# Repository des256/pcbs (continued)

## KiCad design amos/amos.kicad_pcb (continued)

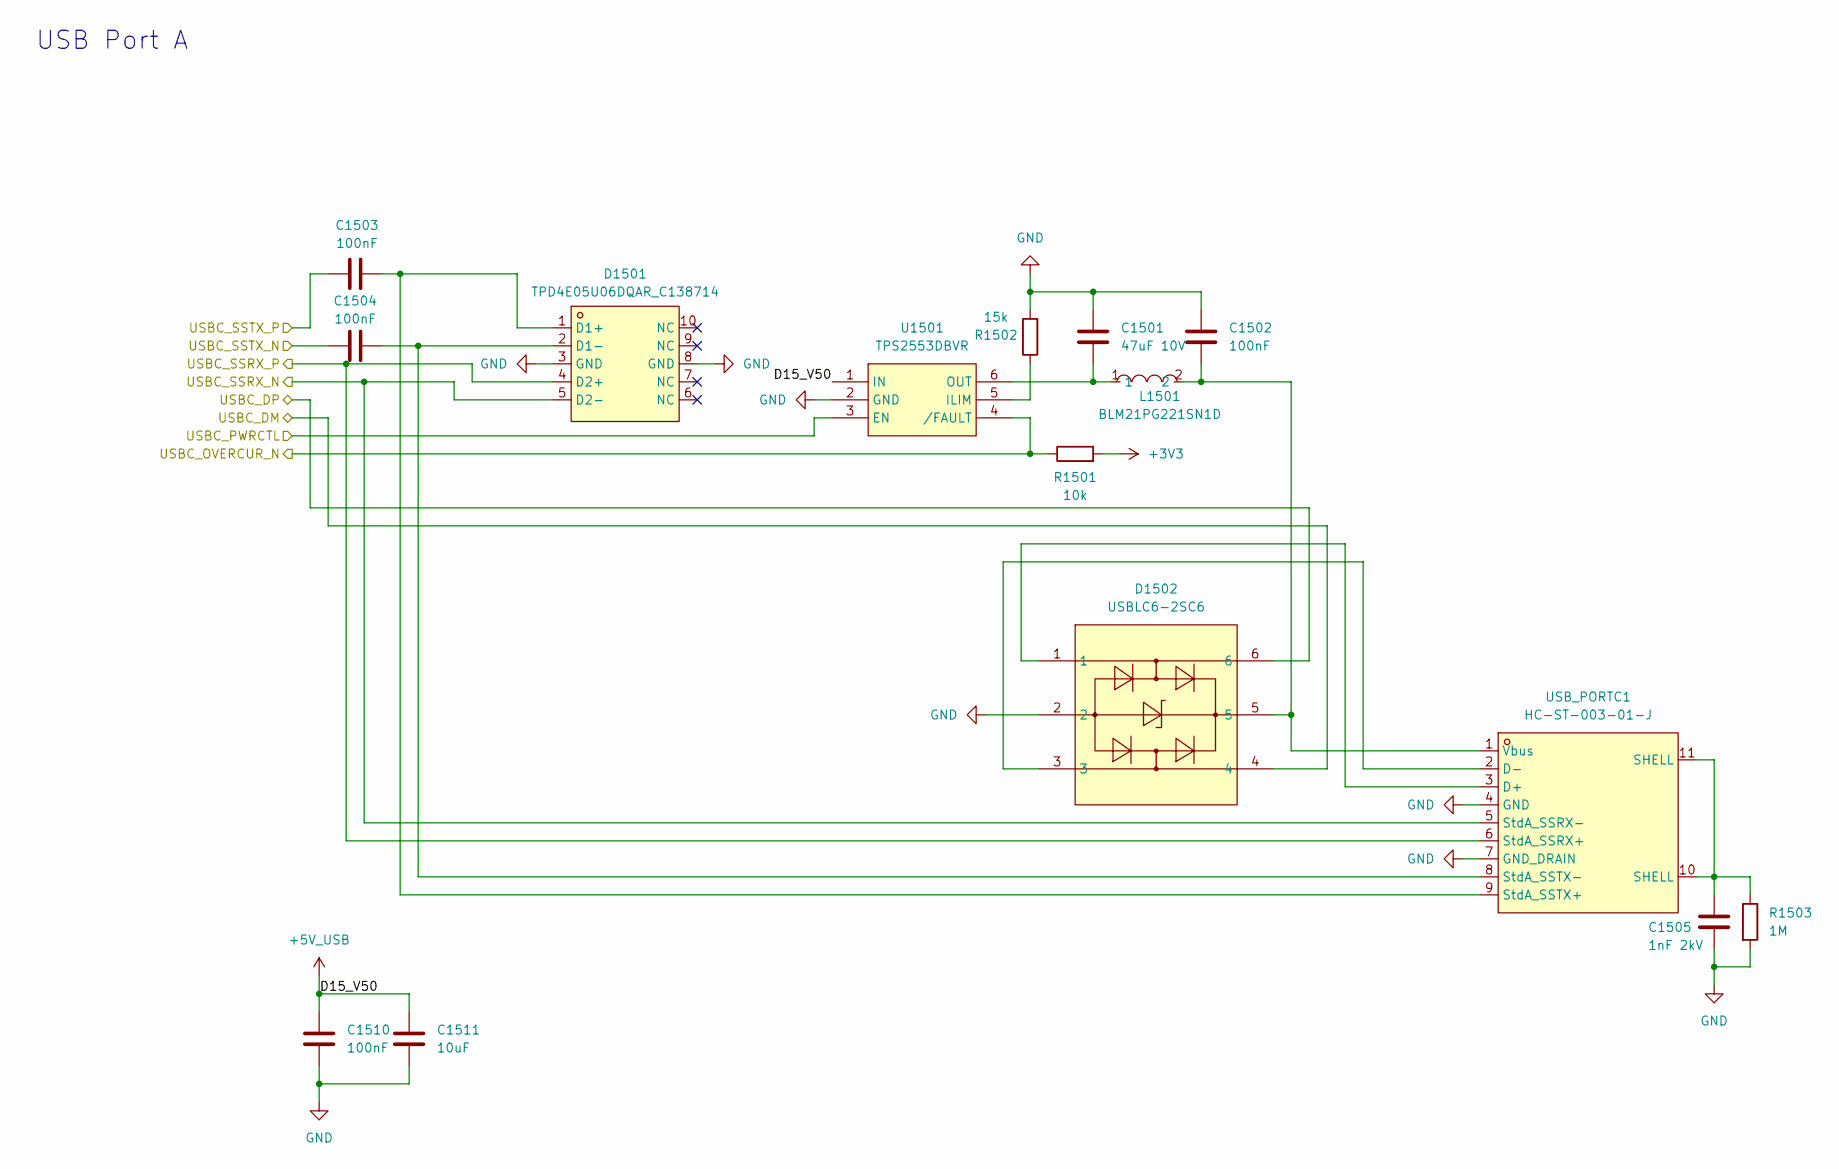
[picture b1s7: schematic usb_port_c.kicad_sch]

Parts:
C1501: 47uF 10V; C_1206_3216Metric; LCSC C96123
C1502, C1503, C1504: 100nF; C_0402_1005Metric; LCSC C307331
C1505: 1nF 2kV; C_1206_3216Metric; LCSC C9196
C1510: 100nF; C_0402_1005Metric; LCSC Part C14663
C1511: 10uF; C_0805_2012Metric; LCSC Part C15850
D1501: TPD4E05U06DQAR_C138714; USON-10_L2.5-W1.0-P0.50-BL; MPN TPD4E05U06DQAR; LCSC Part C138714
D1502: USBLC6-2SC6; SOT-23-6_L2.9-W1.6-P0.95-LS2.8-BL; MPN USBLC6-2SC6; LCSC Part C7519
L1501: BLM21PG221SN1D; L0805; MPN BLM21PG221SN1D; LCSC Part C85840
R1501: 10k; R_0402_1005Metric; LCSC C25744
R1502: 15k; R_0402_1005Metric; LCSC C25756
R1503: 1M; R_0402_1005Metric; LCSC C26083
U1501: TPS2553DBVR; SOT-23-6_L2.9-W1.6-P0.95-LS2.8-BR; MPN TPS2553DBVR; LCSC Part C55266
USB_PORTC1: HC-ST-003-01-J; USB-3.0-A-TH_HC-ST-003-01-Z; MPN HC-ST-003-01-J; LCSC Part C2845330

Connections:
+3V3: R1501.2; also elsewhere on the board
+5V_USB: C1510.1, C1511.1, U1501.1 (IN); also elsewhere on the board
/USBC_DM: D1502.4; also elsewhere on the board
/USBC_DP: D1502.6; also elsewhere on the board
/USBC_OVERCUR_N: R1501.1, U1501.4 (/FAULT); also elsewhere on the board
/USBC_PWRCTL: U1501.3 (EN); also elsewhere on the board
/USBC_SSRX_N: D1501.5 (D2-), USB_PORTC1.5 (StdA_SSRX-); also elsewhere on the board
/USBC_SSRX_P: D1501.4 (D2+), USB_PORTC1.6 (StdA_SSRX+); also elsewhere on the board
/USBC_SSTX_N: C1504.1; also elsewhere on the board
/USBC_SSTX_P: C1503.2; also elsewhere on the board
GND: C1501.1, C1502.1, C1505.2, C1510.2, C1511.2, D1501.3 (GND), D1501.8 (GND), D1502.2, R1502.2, R1503.2, U1501.2 (GND), USB_PORTC1.4 (GND), USB_PORTC1.7 (GND_DRAIN); also elsewhere on the board
unnamed: C1505.1, R1503.1, USB_PORTC1.10 (SHELL), USB_PORTC1.11 (SHELL)
unnamed: C1503.1, D1501.1 (D1+), USB_PORTC1.9 (StdA_SSTX+)
unnamed: C1504.2, D1501.2 (D1-), USB_PORTC1.8 (StdA_SSTX-)
unnamed: R1502.1, U1501.5 (ILIM)
unnamed: C1501.2, L1501.1, U1501.6 (OUT)
unnamed: D1502.1, USB_PORTC1.3 (D+)
unnamed: D1502.3, USB_PORTC1.2 (D-)
unnamed: C1502.2, D1502.5, L1501.2, USB_PORTC1.1 (Vbus)

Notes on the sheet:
USB Port A

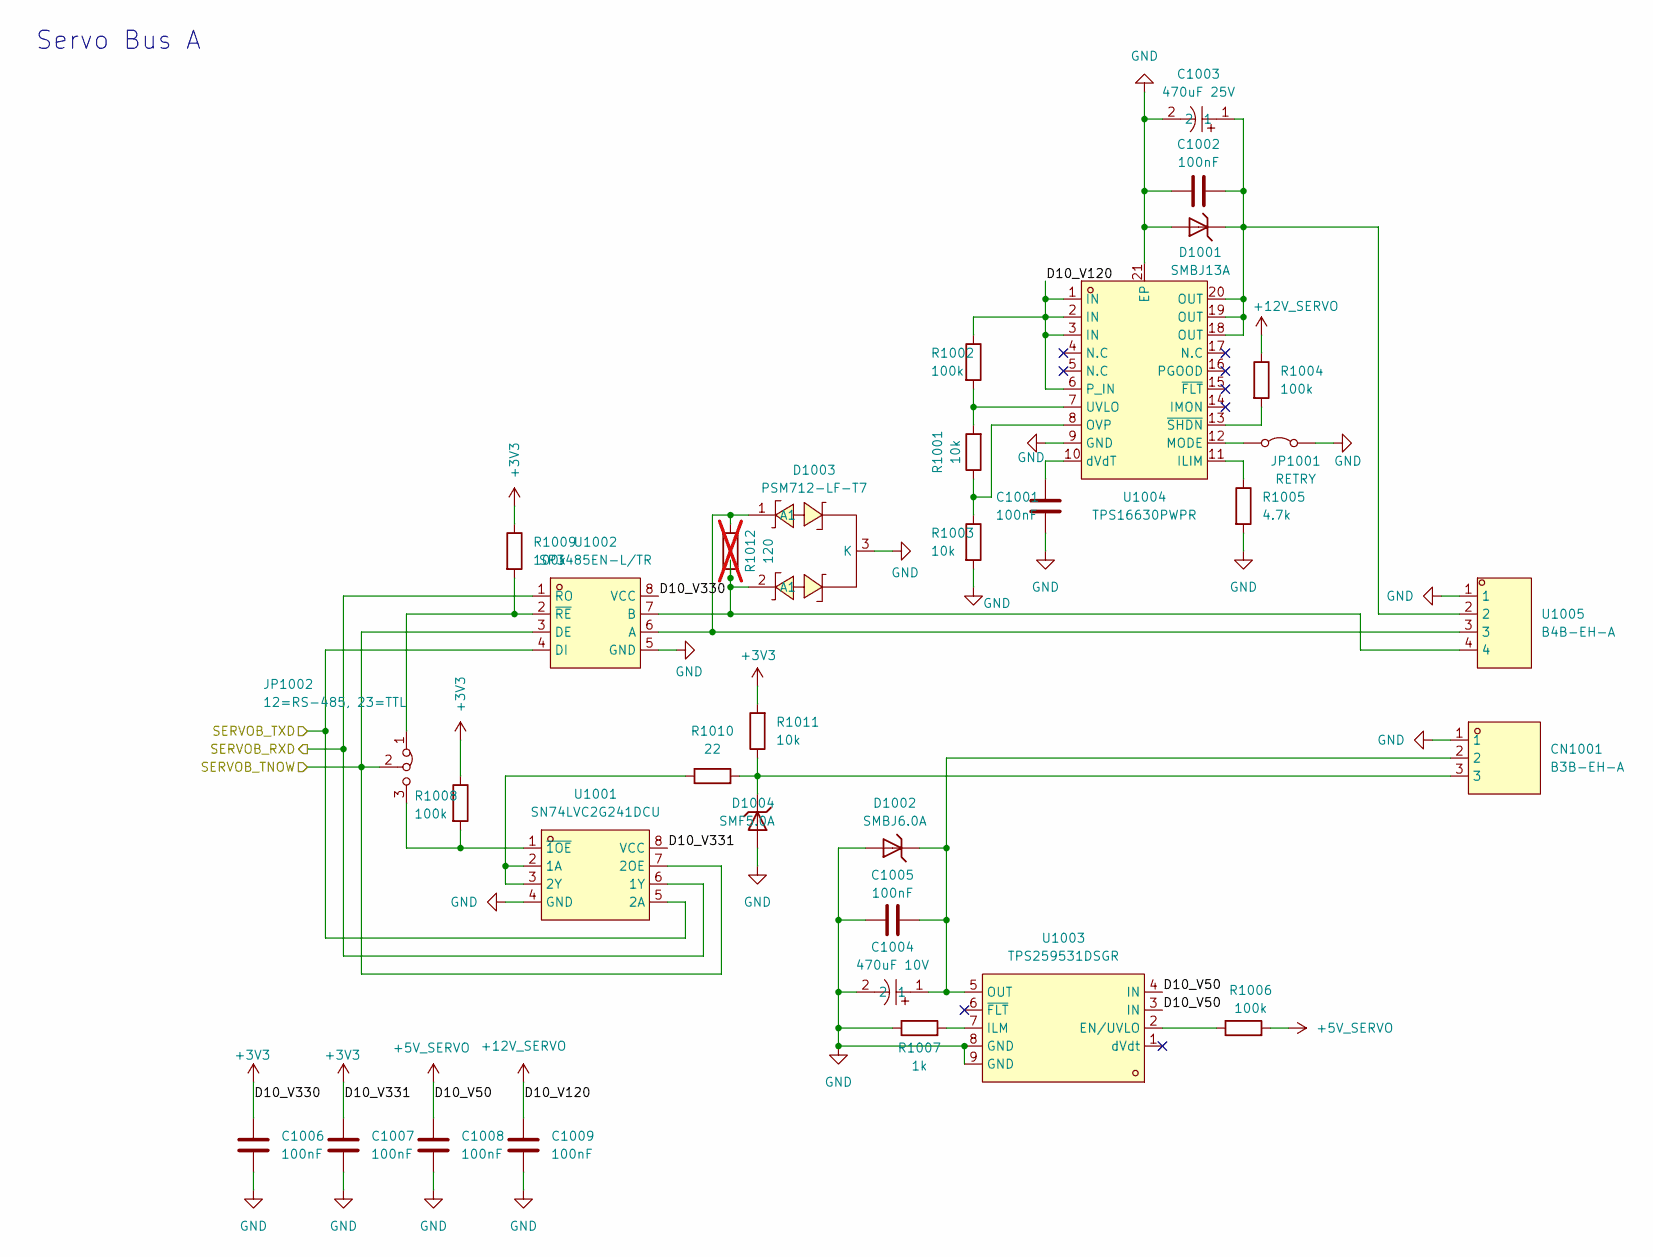
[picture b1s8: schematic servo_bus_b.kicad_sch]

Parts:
C1001, C1002, C1005: 100nF; C_0402_1005Metric; LCSC C307331
C1003: 470uF 25V; CP_Elec_8x10.5; LCSC C46550466
C1004: 470uF 10V; CP_Elec_6.3x7.7; LCSC C46550459
C1006, C1007, C1008, C1009: 100nF; C_0402_1005Metric; LCSC Part C14663
CN1001: B3B-EH-A; CONN-TH_B3B-EH-A-LF-SN; MPN B3B-EH-A(LF)(SN); LCSC Part C160259
D1001: SMBJ13A; SMB_L4.4-W3.6-LS5.3-RD; LCSC C19077567
D1002: SMBJ6.0A; SMB_L4.4-W3.6-LS5.3-RD; LCSC C19077560
D1003: PSM712-LF-T7; SOT-23-3_L3.0-W1.7-P0.95-LS2.9-BR; MPN PSM712-LF-T7; LCSC Part C32677
D1004: SMF5.0A; SOD-123FL_L2.8-W1.9-LS3.7-RD; LCSC C19077497
JP1001: RETRY; PinHeader_1x02_P2.54mm_Vertical; MPN PZ254V-11-02P; LCSC Part C492401
JP1002: 12=RS-485, 23=TTL; PinHeader_1x03_P2.54mm_Vertical; MPN PZ254V-11-03P; LCSC Part C2937625
R1001, R1003, R1011: 10k; R_0402_1005Metric; LCSC C25744
R1002, R1004, R1006, R1008, R1009: 100k; R_0402_1005Metric; LCSC C25741
R1005: 4.7k; R_0402_1005Metric; LCSC C25900
R1007: 1k; R_0402_1005Metric; LCSC C11702
R1010: 22; R_0402_1005Metric; LCSC C25092
R1012: 120; R_0603; LCSC C22787; not fitted
U1001: SN74LVC2G241DCU; VSSOP-8_L2.3-W2.0-P0.50-LS3.1-BR; MPN SN74LVC2G241DCUR; LCSC Part C10430
U1002: SP3485EN-L/TR; SOIC-8_L5.0-W4.0-P1.27-LS6.0-BL; MPN SP3485EN-L/TR; LCSC Part C8963
U1003: TPS259531DSGR; WSON-8_L2.0-W2.0-P0.50-TL-EP; MPN TPS259531DSGR; LCSC Part C2155674
U1004: TPS16630PWPR; HTSSOP-20_L6.5-W4.4-P0.65-LS6.4-TL-EP2.58; MPN TPS16630PWPR; LCSC Part C1849461
U1005: B4B-EH-A; CONN-TH_B4B-EH-A-LF-SN; MPN B4B-EH-A(LF)(SN); LCSC Part C160258

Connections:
+3V3: C1006.1, C1007.1, R1008.1, R1009.1, R1011.2, U1001.8 (VCC), U1002.8 (VCC); also elsewhere on the board
+5V_SERVO: C1008.1, R1006.2, U1003.3 (IN), U1003.4 (IN); also elsewhere on the board
+12V_SERVO: C1009.1, R1002.1, R1004.1, U1004.1 (IN), U1004.2 (IN), U1004.3 (IN), U1004.6 (P_IN); also elsewhere on the board
/SERVOB_RXD: U1001.6 (1Y), U1002.1 (RO); also elsewhere on the board
/SERVOB_TNOW: JP1002.2 (C), U1001.7 (2OE), U1002.3 (DE); also elsewhere on the board
/SERVOB_TXD: U1001.5 (2A), U1002.4 (DI); also elsewhere on the board
GND: C1001.2, C1002.1, C1003.2, C1004.2, C1005.1, C1006.2, C1007.2, C1008.2, C1009.2, CN1001.1, D1001.2, D1002.2, D1003.3 (K), D1004.2, JP1001.2 (B), R1003.2, R1005.2, R1007.1, U1001.4 (GND), U1002.5 (GND), U1003.8 (GND), U1003.9 (GND), U1004.9 (GND), U1004.21 (EP), U1005.1; also elsewhere on the board
unnamed: C1002.2, C1003.1, D1001.1, U1004.18 (OUT), U1004.19 (OUT), U1004.20 (OUT), U1005.2
unnamed: CN1001.3, D1004.1, R1010.2, R1011.1
unnamed: JP1001.1 (A), U1004.12 (MODE)
unnamed: JP1002.1 (A), R1009.2, U1002.2 (~RE)
unnamed: JP1002.3 (B), R1008.2, U1001.1 (~1OE)
unnamed: R1010.1, U1001.2 (1A), U1001.3 (2Y)
unnamed: D1003.1 (A1), R1012.1, U1002.6 (A), U1005.3
unnamed: D1003.2 (A1), R1012.2, U1002.7 (B), U1005.4
unnamed: R1006.1, U1003.2 (EN/UVLO)
unnamed: R1007.2, U1003.7 (ILM)
unnamed: C1004.1, C1005.2, CN1001.2, D1002.1, U1003.5 (OUT)
unnamed: R1005.1, U1004.11 (ILIM)
unnamed: R1001.1, R1003.1, U1004.8 (OVP)
unnamed: R1001.2, R1002.2, U1004.7 (UVLO)
unnamed: C1001.1, U1004.10 (dVdT)
unnamed: R1004.2, U1004.13 (~SHDN)

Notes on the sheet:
Servo Bus A

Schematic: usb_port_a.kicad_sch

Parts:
C1301: 47uF 10V; C_1206_3216Metric; LCSC C96123
C1302, C1303, C1304: 100nF; C_0402_1005Metric; LCSC C307331
C1305: 1nF 2kV; C_1206_3216Metric; LCSC C9196
C1306: 100nF; C_0402_1005Metric; LCSC Part C14663
C1307: 10uF; C_0805_2012Metric; LCSC Part C15850
D1301: TPD4E05U06DQAR_C138714; USON-10_L2.5-W1.0-P0.50-BL; MPN TPD4E05U06DQAR; LCSC Part C138714
D1302: USBLC6-2SC6; SOT-23-6_L2.9-W1.6-P0.95-LS2.8-BL; MPN USBLC6-2SC6; LCSC Part C7519
L1301: BLM21PG221SN1D; L0805; MPN BLM21PG221SN1D; LCSC Part C85840
R1301: 10k; R_0402_1005Metric; LCSC C25744
R1302: 15k; R_0402_1005Metric; LCSC C25756
R1303: 1M; R_0402_1005Metric; LCSC C26083
U1301: TPS2553DBVR; SOT-23-6_L2.9-W1.6-P0.95-LS2.8-BR; MPN TPS2553DBVR; LCSC Part C55266
USB_PORTA1: HC-ST-003-01-J; USB-3.0-A-TH_HC-ST-003-01-Z; MPN HC-ST-003-01-J; LCSC Part C2845330

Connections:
+3V3: R1301.2; also elsewhere on the board
+5V_USB: C1306.1, C1307.1, U1301.1 (IN); also elsewhere on the board
/USBA_DM: D1302.4; also elsewhere on the board
/USBA_DP: D1302.6; also elsewhere on the board
/USBA_OVERCUR_N: R1301.1, U1301.4 (/FAULT); also elsewhere on the board
/USBA_PWRCTL: U1301.3 (EN); also elsewhere on the board
/USBA_SSRX_N: D1301.5 (D2-), USB_PORTA1.5 (StdA_SSRX-); also elsewhere on the board
/USBA_SSRX_P: D1301.4 (D2+), USB_PORTA1.6 (StdA_SSRX+); also elsewhere on the board
/USBA_SSTX_N: C1304.1; also elsewhere on the board
/USBA_SSTX_P: C1303.2; also elsewhere on the board
GND: C1301.1, C1302.1, C1305.2, C1306.2, C1307.2, D1301.3 (GND), D1301.8 (GND), D1302.2, R1302.2, R1303.2, U1301.2 (GND), USB_PORTA1.4 (GND), USB_PORTA1.7 (GND_DRAIN); also elsewhere on the board
unnamed: C1305.1, R1303.1, USB_PORTA1.10 (SHELL), USB_PORTA1.11 (SHELL)
unnamed: C1303.1, D1301.1 (D1+), USB_PORTA1.9 (StdA_SSTX+)
unnamed: C1304.2, D1301.2 (D1-), USB_PORTA1.8 (StdA_SSTX-)
unnamed: R1302.1, U1301.5 (ILIM)
unnamed: C1301.2, L1301.1, U1301.6 (OUT)
unnamed: D1302.1, USB_PORTA1.3 (D+)
unnamed: D1302.3, USB_PORTA1.2 (D-)
unnamed: C1302.2, D1302.5, L1301.2, USB_PORTA1.1 (Vbus)

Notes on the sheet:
USB Port A

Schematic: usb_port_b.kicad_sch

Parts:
C1401: 47uF 10V; C_1206_3216Metric; LCSC C96123
C1402, C1403, C1404: 100nF; C_0402_1005Metric; LCSC C307331
C1405: 1nF 2kV; C_1206_3216Metric; LCSC C9196
C1408: 100nF; C_0402_1005Metric; LCSC Part C14663
C1409: 10uF; C_0805_2012Metric; LCSC Part C15850
D1401: TPD4E05U06DQAR_C138714; USON-10_L2.5-W1.0-P0.50-BL; MPN TPD4E05U06DQAR; LCSC Part C138714
D1402: USBLC6-2SC6; SOT-23-6_L2.9-W1.6-P0.95-LS2.8-BL; MPN USBLC6-2SC6; LCSC Part C7519
L1401: BLM21PG221SN1D; L0805; MPN BLM21PG221SN1D; LCSC Part C85840
R1401: 10k; R_0402_1005Metric; LCSC C25744
R1402: 15k; R_0402_1005Metric; LCSC C25756
R1403: 1M; R_0402_1005Metric; LCSC C26083
U1401: TPS2553DBVR; SOT-23-6_L2.9-W1.6-P0.95-LS2.8-BR; MPN TPS2553DBVR; LCSC Part C55266
USB_PORTB1: HC-ST-003-01-J; USB-3.0-A-TH_HC-ST-003-01-Z; MPN HC-ST-003-01-J; LCSC Part C2845330

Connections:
+3V3: R1401.2; also elsewhere on the board
+5V_USB: C1408.1, C1409.1, U1401.1 (IN); also elsewhere on the board
/USBB_DM: D1402.4; also elsewhere on the board
/USBB_DP: D1402.6; also elsewhere on the board
/USBB_OVERCUR_N: R1401.1, U1401.4 (/FAULT); also elsewhere on the board
/USBB_PWRCTL: U1401.3 (EN); also elsewhere on the board
/USBB_SSRX_N: D1401.5 (D2-), USB_PORTB1.5 (StdA_SSRX-); also elsewhere on the board
/USBB_SSRX_P: D1401.4 (D2+), USB_PORTB1.6 (StdA_SSRX+); also elsewhere on the board
/USBB_SSTX_N: C1404.1; also elsewhere on the board
/USBB_SSTX_P: C1403.2; also elsewhere on the board
GND: C1401.1, C1402.1, C1405.2, C1408.2, C1409.2, D1401.3 (GND), D1401.8 (GND), D1402.2, R1402.2, R1403.2, U1401.2 (GND), USB_PORTB1.4 (GND), USB_PORTB1.7 (GND_DRAIN); also elsewhere on the board
unnamed: C1405.1, R1403.1, USB_PORTB1.10 (SHELL), USB_PORTB1.11 (SHELL)
unnamed: C1403.1, D1401.1 (D1+), USB_PORTB1.9 (StdA_SSTX+)
unnamed: C1404.2, D1401.2 (D1-), USB_PORTB1.8 (StdA_SSTX-)
unnamed: R1402.1, U1401.5 (ILIM)
unnamed: C1401.2, L1401.1, U1401.6 (OUT)
unnamed: D1402.1, USB_PORTB1.3 (D+)
unnamed: D1402.3, USB_PORTB1.2 (D-)
unnamed: C1402.2, D1402.5, L1401.2, USB_PORTB1.1 (Vbus)

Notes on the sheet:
USB Port A

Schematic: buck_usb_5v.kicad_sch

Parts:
C501: 4.7nF; C_0402_1005Metric; LCSC C1538
C502: 47pF; C_0402_1005Metric; LCSC C1567
C503: 100nF; C_0402_1005Metric; LCSC C307331
C504, C505, C506, C507: 2.2uF 50V; C_1206_3216Metric; LCSC Part C50254
C508, C509, C510, C511, C512, C513: 47uF 10V; C_1206_3216Metric; LCSC Part C96123
D501: B560C; SMC_L7.1-W6.2-LS8.1-RD; MPN B560C-13-F; LCSC Part C85100
D502: LED Green; LED_0805_2012Metric; LCSC C2297
L501: 7.2uH 6A; IND-SMD_L10.2-W10.2_7447798720; MPN 7447798720; LCSC Part C105681
R501: 442k; R_0402_1005Metric; LCSC C5101; not fitted
R502: 90.9k; R_0402_1005Metric; LCSC C26989; not fitted
R503: 200k; R_0402_1005Metric; LCSC C25764
R504: 15k; R_0402_1005Metric; LCSC C25756
R505: 53.6k; R_0402_1005Metric; LCSC C453713
R506: 10k; R_0402_1005Metric; LCSC C25744
R507: 1k; R_0402_1005Metric; LCSC C11702
TP501: +5V_USB; TestPoint_Pad_1.0x1.0mm
U501: TPS54560DDAR; SOIC-8_L5.0-W4.0-P1.27-LS6.0-BL-EP2.0; MPN TPS54560DDAR; LCSC Part C31966

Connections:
+5V_USB: C508.1, C509.1, C510.1, C511.1, C512.1, C513.1, L501.2, R505.2, R507.2, TP501.1 (1_1); also elsewhere on the board
+19V: C504.1, C505.1, C506.1, C507.1, R501.1, U501.2 (VIN); also elsewhere on the board
GND: C501.1, C502.2, C504.2, C505.2, C506.2, C507.2, C508.2, C509.2, C510.2, C511.2, C512.2, C513.2, D501.2 (A), D502.1 (K), R502.2, R503.2, R506.2, U501.7 (GND), U501.9 (EP); also elsewhere on the board
unnamed: C501.2, R504.2
unnamed: C503.2, D501.1 (K), L501.1, U501.8 (SW)
unnamed: D502.2 (A), R507.1
unnamed: C503.1, U501.1 (BOOT)
unnamed: C502.1, R504.1, U501.6 (COMP)
unnamed: R501.2, R502.1, U501.3 (EN)
unnamed: R505.1, R506.1, U501.5 (FB)
unnamed: R503.1, U501.4 (RT/CLK)

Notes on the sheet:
5V Buck Converter for USB Devices

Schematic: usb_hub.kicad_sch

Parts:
C701, C702: 30pF; C_0402_1005Metric; LCSC Part C1658
C703, C708, C718: 10uF; C_0805_2012Metric; LCSC Part C15850
C704, C706, C707, C709, C710, C711, C712, C713, C714, C715, C716: 100nF; C_0402_1005Metric; LCSC Part C14663
C705: 4.7uF; C_0805_2012Metric; LCSC Part C1779
C717: 22uF; C_0805_2012Metric; LCSC Part C45783
FB701: BLM18PG121SN1D; L0603; LCSC C14709
R701: 9.53k; R_0402_1005Metric; LCSC C96273
R702: 1M; R_0402_1005Metric; LCSC C26083
R703, R705, R706, R707, R708: 10k; R_0402_1005Metric; LCSC C25744
R704: 90.9k; R_0402_1005Metric; LCSC C26989
TP701: GRSTz; TestPoint_Pad_1.0x1.0mm
U701: TUSB8041IRGCR; QFN-64_L9.0-W9.0-P0.50-BL-EP7.2; MPN TUSB8041IRGCR; LCSC Part C544686
Y701: 24MHz 18pF; OSC-SMD_4P-L3.2-W2.5-BL; LCSC C70571

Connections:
+1V1: C717.1, FB701.2; also elsewhere on the board
+3V3: C704.1, C705.1, C706.1, C707.1, C708.1, R703.2, R706.1, R707.2, R708.2, U701.16 (VDD33), U701.34 (VDD33), U701.52 (VDD33), U701.63 (VDD33); also elsewhere on the board
/SERVO_DM: U701.25 (USB_DM_DN4); also elsewhere on the board
/SERVO_DP: U701.24 (USB_DP_DN4); also elsewhere on the board
/USB Hub/D7_V110: C709.1, C710.1, C711.1, C712.1, C713.1, C714.1, C715.1, C716.1, C718.1, FB701.1, U701.5 (VDD), U701.8 (VDD), U701.13 (VDD), U701.21 (VDD), U701.28 (VDD), U701.31 (VDD), U701.51 (VDD), U701.57 (VDD)
/USBA_DM: U701.2 (USB_DM_DN1); also elsewhere on the board
/USBA_DP: U701.1 (USB_DP_DN1); also elsewhere on the board
/USBA_OVERCUR_N: R708.1, U701.46 (OVERCUR1z); also elsewhere on the board
/USBA_PWRCTL: U701.36 (PWRCTL1/BATEN1); also elsewhere on the board
/USBA_SSRX_N: U701.7 (USB_SSRXM_DN1); also elsewhere on the board
/USBA_SSRX_P: U701.6 (USB_SSRXP_DN1); also elsewhere on the board
/USBA_SSTX_N: U701.4 (USB_SSTXM_DN1); also elsewhere on the board
/USBA_SSTX_P: U701.3 (USB_SSTXP_DN1); also elsewhere on the board
/USBB_DM: U701.10 (USB_DM_DN2); also elsewhere on the board
/USBB_DP: U701.9 (USB_DP_DN2); also elsewhere on the board
/USBB_OVERCUR_N: R707.1, U701.47 (OVERCUR2z); also elsewhere on the board
/USBB_PWRCTL: U701.35 (PWRCTL2/BATEN2); also elsewhere on the board
/USBB_SSRX_N: U701.15 (USB_SSRXM_DN2); also elsewhere on the board
/USBB_SSRX_P: U701.14 (USB_SSRXP_DN2); also elsewhere on the board
/USBB_SSTX_N: U701.12 (USB_SSTXM_DN2); also elsewhere on the board
/USBB_SSTX_P: U701.11 (USB_SSTXP_DN2); also elsewhere on the board
/USBC_DM: U701.18 (USB_DM_DN3); also elsewhere on the board
/USBC_DP: U701.17 (USB_DP_DN3); also elsewhere on the board
/USBC_OVERCUR_N: R706.2, U701.44 (OVERCUR3z); also elsewhere on the board
/USBC_PWRCTL: U701.33 (PWRCTL3/BATEN3); also elsewhere on the board
/USBC_SSRX_N: U701.23 (USB_SSRXM_DN3); also elsewhere on the board
/USBC_SSRX_P: U701.22 (USB_SSRXP_DN3); also elsewhere on the board
/USBC_SSTX_N: U701.20 (USB_SSTXM_DN3); also elsewhere on the board
/USBC_SSTX_P: U701.19 (USB_SSTXP_DN3); also elsewhere on the board
/USBU_DM: U701.54 (USB_DM_UP); also elsewhere on the board
/USBU_DP: U701.53 (USB_DP_UP); also elsewhere on the board
/USBU_SSRX_M: U701.59 (USB_SSRXM_UP); also elsewhere on the board
/USBU_SSRX_P: U701.58 (USB_SSRXP_UP); also elsewhere on the board
/USBU_SSTX_M: U701.56 (USB_SSTXM_UP); also elsewhere on the board
/USBU_SSTX_P: U701.55 (USB_SSTXP_UP); also elsewhere on the board
/USB_VBUS: R704.2; also elsewhere on the board
GND: C701.1, C702.1, C703.2, C704.2, C705.2, C706.2, C707.2, C708.2, C709.2, C710.2, C711.2, C712.2, C713.2, C714.2, C715.2, C716.2, C717.2, C718.2, R701.2, R705.2, U701.49 (TEST), U701.65 (VSS), Y701.2 (GND), Y701.4 (GND); also elsewhere on the board
unnamed: C703.1, R703.1, TP701.1 (1_1), U701.50 (GRSTz)
unnamed: R701.1, U701.64 (USB_R1)
unnamed: R704.1, R705.1, U701.48 (USB_VBUS)
unnamed: C701.2, R702.1, U701.62 (XI), Y701.1 (OSC)
unnamed: C702.2, R702.2, U701.61 (XO), Y701.3 (OSC)

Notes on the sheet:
USB Hub

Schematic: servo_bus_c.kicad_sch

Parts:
C1101, C1102, C1105: 100nF; C_0402_1005Metric; LCSC C307331
C1103: 470uF 25V; CP_Elec_8x10.5; LCSC C46550466
C1104: 470uF 10V; CP_Elec_6.3x7.7; LCSC C46550459
C1106, C1107, C1108, C1109: 100nF; C_0402_1005Metric; LCSC Part C14663
CN1101: B3B-EH-A; CONN-TH_B3B-EH-A-LF-SN; MPN B3B-EH-A(LF)(SN); LCSC Part C160259
D1101: SMBJ13A; SMB_L4.4-W3.6-LS5.3-RD; LCSC C19077567
D1102: SMBJ6.0A; SMB_L4.4-W3.6-LS5.3-RD; LCSC C19077560
D1103: PSM712-LF-T7; SOT-23-3_L3.0-W1.7-P0.95-LS2.9-BR; MPN PSM712-LF-T7; LCSC Part C32677
D1104: SMF5.0A; SOD-123FL_L2.8-W1.9-LS3.7-RD; LCSC C19077497
JP1101: RETRY; PinHeader_1x02_P2.54mm_Vertical; MPN PZ254V-11-02P; LCSC Part C492401
JP1102: 12=RS-485, 23=TTL; PinHeader_1x03_P2.54mm_Vertical; MPN PZ254V-11-03P; LCSC Part C2937625
R1101, R1103, R1111: 10k; R_0402_1005Metric; LCSC C25744
R1102, R1104, R1106, R1108, R1109: 100k; R_0402_1005Metric; LCSC C25741
R1105: 4.7k; R_0402_1005Metric; LCSC C25900
R1107: 1k; R_0402_1005Metric; LCSC C11702
R1110: 22; R_0402_1005Metric; LCSC C25092
R1112: 120; R_0603; LCSC C22787; not fitted
U1101: SN74LVC2G241DCU; VSSOP-8_L2.3-W2.0-P0.50-LS3.1-BR; MPN SN74LVC2G241DCUR; LCSC Part C10430
U1102: SP3485EN-L/TR; SOIC-8_L5.0-W4.0-P1.27-LS6.0-BL; MPN SP3485EN-L/TR; LCSC Part C8963
U1103: TPS259531DSGR; WSON-8_L2.0-W2.0-P0.50-TL-EP; MPN TPS259531DSGR; LCSC Part C2155674
U1104: TPS16630PWPR; HTSSOP-20_L6.5-W4.4-P0.65-LS6.4-TL-EP2.58; MPN TPS16630PWPR; LCSC Part C1849461
U1105: B4B-EH-A; CONN-TH_B4B-EH-A-LF-SN; MPN B4B-EH-A(LF)(SN); LCSC Part C160258

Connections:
+3V3: C1106.1, C1107.1, R1108.1, R1109.1, R1111.2, U1101.8 (VCC), U1102.8 (VCC); also elsewhere on the board
+5V_SERVO: C1108.1, R1106.2, U1103.3 (IN), U1103.4 (IN); also elsewhere on the board
+12V_SERVO: C1109.1, R1102.1, R1104.1, U1104.1 (IN), U1104.2 (IN), U1104.3 (IN), U1104.6 (P_IN); also elsewhere on the board
/SERVOC_RXD: U1101.6 (1Y), U1102.1 (RO); also elsewhere on the board
/SERVOC_TNOW: JP1102.2 (C), U1101.7 (2OE), U1102.3 (DE); also elsewhere on the board
/SERVOC_TXD: U1101.5 (2A), U1102.4 (DI); also elsewhere on the board
GND: C1101.2, C1102.1, C1103.2, C1104.2, C1105.1, C1106.2, C1107.2, C1108.2, C1109.2, CN1101.1, D1101.2, D1102.2, D1103.3 (K), D1104.2, JP1101.2 (B), R1103.2, R1105.2, R1107.1, U1101.4 (GND), U1102.5 (GND), U1103.8 (GND), U1103.9 (GND), U1104.9 (GND), U1104.21 (EP), U1105.1; also elsewhere on the board
unnamed: C1102.2, C1103.1, D1101.1, U1104.18 (OUT), U1104.19 (OUT), U1104.20 (OUT), U1105.2
unnamed: CN1101.3, D1104.1, R1110.2, R1111.1
unnamed: JP1101.1 (A), U1104.12 (MODE)
unnamed: JP1102.1 (A), R1109.2, U1102.2 (~RE)
unnamed: JP1102.3 (B), R1108.2, U1101.1 (~1OE)
unnamed: R1110.1, U1101.2 (1A), U1101.3 (2Y)
unnamed: D1103.1 (A1), R1112.1, U1102.6 (A), U1105.3
unnamed: D1103.2 (A1), R1112.2, U1102.7 (B), U1105.4
unnamed: R1106.1, U1103.2 (EN/UVLO)
unnamed: R1107.2, U1103.7 (ILM)
unnamed: C1104.1, C1105.2, CN1101.2, D1102.1, U1103.5 (OUT)
unnamed: R1105.1, U1104.11 (ILIM)
unnamed: R1101.1, R1103.1, U1104.8 (OVP)
unnamed: R1101.2, R1102.2, U1104.7 (UVLO)
unnamed: C1101.1, U1104.10 (dVdT)
unnamed: R1104.2, U1104.13 (~SHDN)

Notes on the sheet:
Servo Bus A

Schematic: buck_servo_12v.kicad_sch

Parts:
C301, C307: 100nF; C_0402_1005Metric; LCSC C307331
C302: 47pF; C_0402_1005Metric; LCSC C1567
C303: 3.3nF; C_0402_1005Metric; LCSC C26404
C304: 680pF; C_0402_1005Metric; LCSC C1541
C305: 4.7uF 16V; C_0603_1608Metric; LCSC C19666
C306: 10pF; C_0402_1005Metric; LCSC C32949
C308: 100pF; C_0603_1608Metric; LCSC C14858; not fitted
C309: 100nF 100V; C_0805_2012Metric; LCSC Part C28233
C310, C311, C312, C313, C314: 4.7uF 50V; C_1206_3216Metric; LCSC Part C29823
C315, C316, C317, C318, C319, C320: 22uF 25V; C_1206_3216Metric; LCSC Part C12891
C321, C322: 470uF 25V; CAP-SMD_BD8.0-L8.3-W8.3-LS9.0-FD_H10.5; LCSC Part C46550466
D301: SS14; D_SMA; LCSC C2480
D302: LED Green; LED_0805_2012Metric; LCSC C2297
JP301: SYNCIN GND OR PGOOD; SolderJumper-3_P1.3mm_Bridged12_Pad1.0x1.5mm
L301: 4.7uH 20A; IND-SMD_L13.5-W12.6; MPN TMPA1265SP-4R7MN-D; LCSC Part C2880057
Q301, Q302: CSD18532Q5B; SON-8_L5.0-W6.0-P1.27-BL-1; MPN CSD18532Q5B; LCSC Part C882766
R301: 100k; R_0402_1005Metric; LCSC C25741
R302: 10k; R_0402_1005Metric; LCSC C25744
R303: 22k; R_0402_1005Metric; LCSC C25768
R304: 15k; R_0402_1005Metric; LCSC C25756
R305: 3.3k; R_0402_1005Metric; LCSC C25890
R306: 200; R_0402_1005Metric; LCSC C25087
R307: 47k; R_0402_1005Metric; LCSC C25792
R308: 20k; R_0402_1005Metric; LCSC C25765
R309: 2.2; R_0402_1005Metric; LCSC C25101
R310: 220; R_0402_1005Metric; LCSC C25091
R311: 4.7k; R_0402_1005Metric; LCSC C25900
R312: 2.2; R_0603; LCSC C22939; not fitted
TP301: +12V_SERVO; TestPoint_Pad_1.0x1.0mm
U301: LM5145RGYR; VQFN-20_L4.5-W3.5-P0.50-BL-EP; MPN LM5145RGYR; LCSC Part C485912

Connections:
+12V_SERVO: C315.1, C316.1, C317.1, C318.1, C319.1, C320.1, C321.1, C322.1, D301.2 (A), L301.2, R306.1, R307.1, R311.1, TP301.1 (1_1); also elsewhere on the board
+19V: C309.1, C310.1, C311.1, C312.1, C313.1, C314.1, Q301.5 (D), Q301.6 (D), Q301.7 (D), Q301.8 (D), Q301.9 (EP), R301.1, U301.20 (VIN); also elsewhere on the board
GND: C301.2, C305.2, C306.2, C308.2, C309.2, C310.2, C311.2, C312.2, C313.2, C314.2, C315.2, C316.2, C317.2, C318.2, C319.2, C320.2, C321.2, C322.2, D302.1 (K), JP301.1 (A), Q302.1 (S), Q302.2 (S), Q302.3 (S), R302.2, R303.1, R305.2, U301.6 (AGND), U301.12 (PGND), U301.15 (EP), U301.21 (EP); also elsewhere on the board
unnamed: C303.2, R304.1
unnamed: C304.1, R306.2
unnamed: C307.1, R309.2
unnamed: C308.1, R312.2
unnamed: C305.1, D301.1 (K), JP301.3 (B), R308.1, U301.14 (VCC)
unnamed: D302.2 (A), R311.2
unnamed: JP301.2 (C), U301.8 (SYNCIN)
unnamed: Q301.4 (G), U301.18 (HO)
unnamed: C307.2, L301.1, Q301.1 (S), Q301.2 (S), Q301.3 (S), Q302.5 (D), Q302.6 (D), Q302.7 (D), Q302.8 (D), Q302.9 (EP), R310.2, R312.1, U301.19 (SW)
unnamed: Q302.4 (G), U301.13 (LO)
unnamed: R309.1, U301.17 (BST)
unnamed: C302.1, R304.2, U301.4 (COMP)
unnamed: R301.2, R302.1, U301.1 (EN/UVLO)
unnamed: C302.2, C303.1, C304.2, R305.1, R307.2, U301.5 (FB)
unnamed: C306.1, R310.1, U301.11 (ILIM)
unnamed: R308.2, U301.10 (PGOOD)
unnamed: R303.2, U301.2 (RT)
unnamed: C301.1, U301.3 (SS/TRK)

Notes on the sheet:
12V Buck Converter for Large Servo

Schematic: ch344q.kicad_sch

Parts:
C801, C802: 33pF; C_0402_1005Metric; LCSC C1562
C803: 100nF; C_0402_1005Metric; LCSC C307331
C804, C805, C806, C807: 100nF; C_0402_1005Metric; LCSC Part C14663
C808: 10uF; C_0805_2012Metric; LCSC Part C15850
D801: USBLC6-2SC6; SOT-23-6_L2.9-W1.6-P0.95-LS2.8-BL; MPN USBLC6-2SC6; LCSC Part C7519
D802: LED Yellow; LED_0805_2012Metric; LCSC C2296
R801: 10k; R_0402_1005Metric; LCSC C25744
R802: 1k; R_0402_1005Metric; LCSC C11702
R803, R804, R805, R806: 4.7k; R_0402_1005Metric; LCSC C25900
TP801: RESET; TestPoint_Pad_1.0x1.0mm
U801: CH344Q_C2988084; LQFP-48_L7.0-W7.0-P0.50-LS9.0-BL; MPN CH344Q; LCSC Part C2988084
Y801: 8MHz 20pF; Crystal_SMD_5032-2Pin_5.0x3.2mm; LCSC C115962

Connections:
+3V3: C804.1, C805.1, C806.1, C807.1, C808.1, D801.5, R801.1, R802.2, U801.9 (VCC), U801.24 (VCC), U801.36 (VCC), U801.48 (VCC); also elsewhere on the board
/SERVOA_RXD: U801.31 (RXD0); also elsewhere on the board
/SERVOA_TNOW: R806.1, U801.39 (TNOW0/GPIO8); also elsewhere on the board
/SERVOA_TXD: U801.30 (TXD0); also elsewhere on the board
/SERVOB_RXD: U801.13 (RXD1); also elsewhere on the board
/SERVOB_TNOW: R803.1, U801.18 (TNOW1/GPIO9); also elsewhere on the board
/SERVOB_TXD: U801.12 (TXD1); also elsewhere on the board
/SERVOC_RXD: U801.22 (RXD2); also elsewhere on the board
/SERVOC_TNOW: R804.1, U801.19 (TNOW2/GPIO10); also elsewhere on the board
/SERVOC_TXD: U801.21 (TXD2); also elsewhere on the board
/SERVOD_RXD: U801.38 (RXD3); also elsewhere on the board
/SERVOD_TNOW: R805.1, U801.34 (TNOW3/DTR3/GPIO11); also elsewhere on the board
/SERVOD_TXD: U801.37 (TXD3); also elsewhere on the board
/SERVO_DM: D801.4; also elsewhere on the board
/SERVO_DP: D801.6; also elsewhere on the board
GND: C801.2, C802.2, C803.1, C804.2, C805.2, C806.2, C807.2, C808.2, D801.2, R803.2, R804.2, R805.2, R806.2, U801.8 (GND), U801.20 (GND), U801.23 (GND), U801.35 (GND), U801.44 (TEST), U801.47 (GND); also elsewhere on the board
unnamed: D802.2 (A), R802.1
unnamed: D802.1 (K), U801.14 (ACT)
unnamed: C803.2, R801.2, TP801.1 (1_1), U801.7 (RESET)
unnamed: D801.1, U801.43 (UD+)
unnamed: D801.3, U801.42 (UD-)
unnamed: C801.1, U801.5 (XI), Y801.1
unnamed: C802.1, U801.6 (XO), Y801.2

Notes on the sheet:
Servo Bus Controller

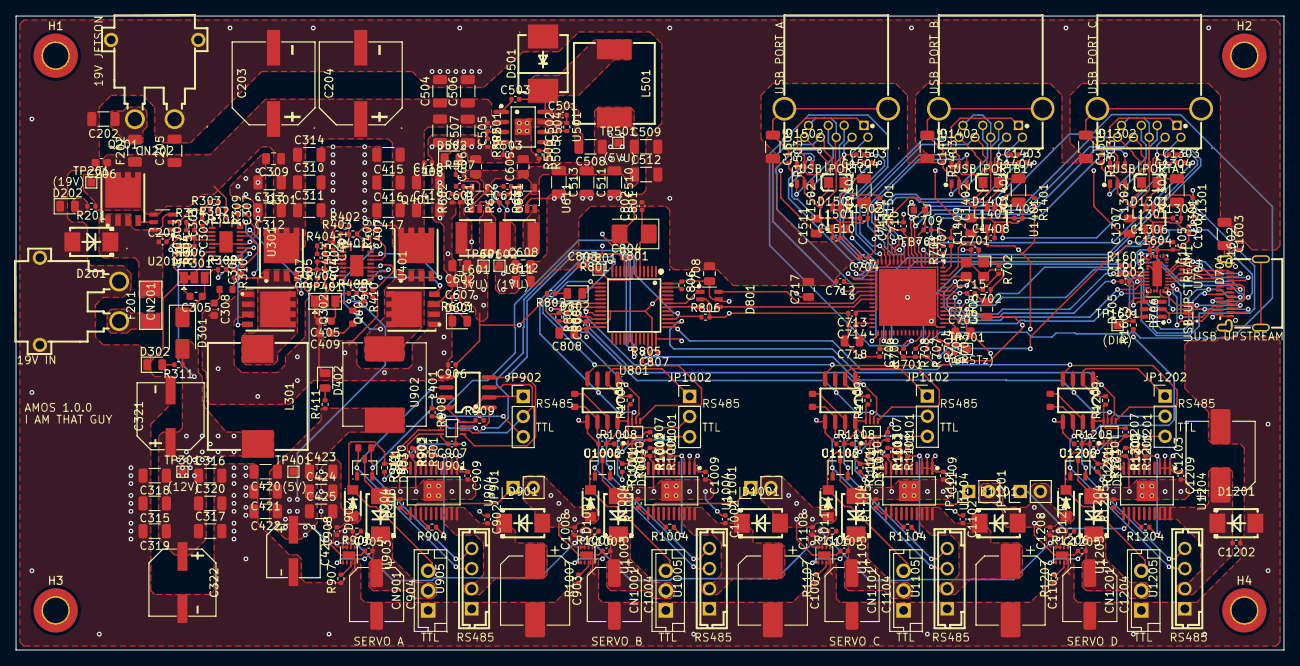
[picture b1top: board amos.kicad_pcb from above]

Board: 4 copper layers, 160.0 x 80.0 mm, 388 parts (0 on the bottom side), 224 nets.

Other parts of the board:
H1, H2, H3, H4: MountingHole_3.2mm_M3_DIN965_Pad_TopBottom

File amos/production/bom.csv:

Designator,Footprint,Quantity,Value,LCSC Part #
"C1001, C1002, C1005, C1101, C1102, C1105, C1201, C1202, C1205, C1302, C1303, C1304, C1402, C1403, C1404, C1502, C1503, C1504, C1601, C1602, C201, C301, C307, C401, C407, C408, C503, C803, C901, C902, C905",0402,31,100nF,C307331
"C1003, C1103, C1203, C903",CP_Elec_8x10.5,4,470uF 25V,C46550466
"C1004, C1104, C1204, C904",CP_Elec_6.3x7.7,4,470uF 10V,C46550459
"C1006, C1007, C1008, C1009, C1106, C1107, C1108, C1109, C1206, C1207, C1208, C1209, C1306, C1408, C1510, C1605, C1607, C704, C706, C707, C709, C710, C711, C712, C713, C714, C715, C716, C804, C805, C806, C807, C906, C907, C908, C909",0402,36,100nF,C14663
"C1301, C1401, C1501, C420, C421, C422, C423, C424, C425, C508, C509, C510, C511, C512, C513",1206,15,47uF 10V,C96123
"C1305, C1405, C1505, C1603",1206,4,1nF 2kV,C9196
"C1307, C1409, C1511, C703, C708, C718, C808",0805,7,10uF,C15850
C1604,0402,1,1uF,C15849
"C202, C205",1206,2,10uF 50V,C13585
"C203, C204",CAP-SMD_BD10.0-L10.3-W10.3-LS11.3-FD,2,470uF 35V,C5155332
C206,0603,1,100nF 50V,C14663
"C302, C502",0402,2,47pF,C1567
C303,0402,1,3.3nF,C26404
C304,0402,1,680pF,C1541
"C305, C405",0603,2,4.7uF 16V,C19666
C306,0402,1,10pF,C32949
C309,0805,1,100nF 100V,C28233
"C310, C311, C312, C313, C314",1206,5,4.7uF 50V,C29823
"C315, C316, C317, C318, C319, C320",1206,6,22uF 25V,C12891
"C321, C322",CAP-SMD_BD8.0-L8.3-W8.3-LS9.0-FD_H10.5,2,470uF 25V,C46550466
C402,0402,1,150pF,C1527
"C403, C501",0402,2,4.7nF,C1538
C404,0402,1,1.8nF,C107024
C406,0402,1,15pF,C1548
"C415, C416, C417, C418, C419, C504, C505, C506, C507",1206,9,2.2uF 50V,C50254
C426,CAP-SMD_BD6.3-L6.6-W6.6-LS7.3-FD-H7.7,1,470uF 10V,C46550459
"C601, C801, C802",0402,3,33pF,C1562
"C602, C607, C608, C612, C717",0805,5,22uF,C45783
"C605, C606, C705",0805,3,4.7uF,C1779
C611,0402,1,100pF,C1546
"C701, C702",0402,2,30pF,C1658
"CN1001, CN1101, CN1201, CN901",CONN-TH_B3B-EH-A-LF-SN,4,B3B-EH-A,C160259
CN201,CONN-TH_XT30PW-M,1,19V INPUT,C431092
CN202,CONN-TH_XT30PW-M,1,19V JETSON,C431092
"D1001, D1101, D1201, D901",SMB_L4.4-W3.6-LS5.3-RD,4,SMBJ13A,C908801
"D1002, D1102, D1202, D902",SMB_L4.4-W3.6-LS5.3-RD,4,SMBJ6.0A,C908801
"D1003, D1103, D1203, D903",SOT-23-3_L3.0-W1.7-P0.95-LS2.9-BR,4,PSM712-LF-T7,C32677
"D1004, D1104, D1204, D904",SOD-123FL_L2.8-W1.9-LS3.7-RD,4,SMF5.0A,C2857263
"D1301, D1401, D1501, D704, D706",USON-10_L2.5-W1.0-P0.50-BL,5,TPD4E05U06DQAR_C138714,C138714
"D1302, D1402, D1502, D705, D801",SOT-23-6_L2.9-W1.6-P0.95-LS2.8-BL,5,USBLC6-2SC6,C7519
D201,SMB_L4.4-W3.6-LS5.3-RD,1,SMBJ24A_C908801,C908801
"D202, D302, D402, D502, D601",0805,5,LED Green,C2297
D301,D_SMA,1,SS14,C2480
D501,SMC_L7.1-W6.2-LS8.1-RD,1,B560C,C85100
D802,0805,1,LED Yellow,C2296
F201,2410,1,15A T 2410,C187551
F202,1206,1,4A T 1206,C3157092
FB701,L0603,1,BLM18PG121SN1D,C80165
"L1301, L1401, L1501",L0805,3,BLM21PG221SN1D,C85840
L301,IND-SMD_L13.5-W12.6,1,4.7uH 20A,C2880057
L401,L_Vishay_IHLP-4040,1,3.3uH 18A,C845075
L501,IND-SMD_L10.2-W10.2_7447798720,1,7.2uH 6A,C105681
"L601, L611",IND-SMD_L4.0-W4.0_LQH44PN2R2MP0L,2,2.2uH 3.4A,C135262
"Q201, Q301, Q302, Q401, Q402",SON-8_L5.0-W6.0-P1.27-BL-1,5,CSD18532Q5B,C882766
"R1001, R1003, R1011, R1101, R1103, R1111, R1201, R1203, R1211, R1301, R1401, R1501, R201, R302, R402, R506, R611, R703, R705, R706, R707, R708, R801, R901, R903, R911",0402,26,10k,C25744
"R1002, R1004, R1006, R1008, R1009, R1102, R1104, R1106, R1108, R1109, R1202, R1204, R1206, R1208, R1209, R301, R401, R601, R902, R904, R906, R908, R909",0402,23,100k,C25741
"R1005, R1105, R1205, R311, R803, R804, R805, R806, R905",0402,9,4.7k,C25900
"R1007, R1107, R1207, R406, R411, R507, R603, R802, R907",0402,9,1k,C11702
"R1010, R1110, R1210, R910",0402,4,22,C25092
"R1302, R1402, R1502, R304, R504",0402,5,15k,C25756
"R1303, R1403, R1503, R1602, R702",0402,5,1M,C26083
R1601,0402,1,910k,C25800
"R1603, R503",0402,2,200k,C25764
"R303, R602",0402,2,22k,C25768
R305,0402,1,3.3k,C25890
R306,0402,1,200,C25087
R307,0402,1,47k,C25792
"R308, R408",0402,2,20k,C25765
"R309, R409",0402,2,2.2,C25101
R310,0402,1,220,C25091
R403,0402,1,49.9k,C25897
R404,0402,1,11k,C25749
"R405, R612",0402,2,12k,C25752
R407,0402,1,2.2k,C25879
R410,0402,1,150,C25082
R505,0402,1,53.6k,C453713
R701,0402,1,9.53k,C96273
R704,0402,1,90.9k,C26989
"U1001, U1101, U1201, U901",VSSOP-8_L2.3-W2.0-P0.50-LS3.1-BR,4,SN74LVC2G241DCU,C10430
"U1002, U1102, U1202, U902",SOIC-8_L5.0-W4.0-P1.27-LS6.0-BL,4,SP3485EN-L/TR,C8963
"U1003, U1103, U1203, U903",WSON-8_L2.0-W2.0-P0.50-TL-EP,4,TPS259531DSGR,C2155674
"U1004, U1104, U1204, U904",HTSSOP-20_L6.5-W4.4-P0.65-LS6.4-TL-EP2.58,4,TPS16630PWPR,C1849461
"U1005, U1105, U1205, U905",CONN-TH_B4B-EH-A-LF-SN,4,B4B-EH-A,C160258
"U1301, U1401, U1501",SOT-23-6_L2.9-W1.6-P0.95-LS2.8-BR,3,TPS2553DBVR,C55266
U201,SOT-23-6_L2.9-W1.6-P0.95-LS2.8-TL,1,LM74700QDBVTQ1,C2653623
"U301, U401",VQFN-20_L4.5-W3.5-P0.50-BL-EP,2,LM5145RGYR,C485912
U501,SOIC-8_L5.0-W4.0-P1.27-LS6.0-BL-EP2.0,1,TPS54560DDAR,C31966
"U601, U611",SOT-23-5_L3.0-W1.7-P0.95-LS2.8-BR,2,TLV62569DBVR,C141836
U701,QFN-64_L9.0-W9.0-P0.50-BL-EP7.2,1,TUSB8041IRGCR,C544686
U704,WQFN-30_L4.5-W2.5-P0.4-BL-EP,1,HD3SS3220RNHR,C165155
U801,LQFP-48_L7.0-W7.0-P0.50-LS9.0-BL,1,CH344Q_C2988084,C2988084
"USB_PORTA1, USB_PORTB1, USB_PORTC1",USB-3.0-A-TH_HC-ST-003-01-Z,3,HC-ST-003-01-J,C2845330
USB_UPSTREAM1,USB-C-SMD_TYPE-C-24P-QT,1,TYPE-C 24P QT,C2681555
Y701,OSC-SMD_4P-L3.2-W2.5-BL,1,24MHz 18pF,C70571
Y801,Crystal_SMD_5032-2Pin_5.0x3.2mm,1,8MHz 20pF,C115962
